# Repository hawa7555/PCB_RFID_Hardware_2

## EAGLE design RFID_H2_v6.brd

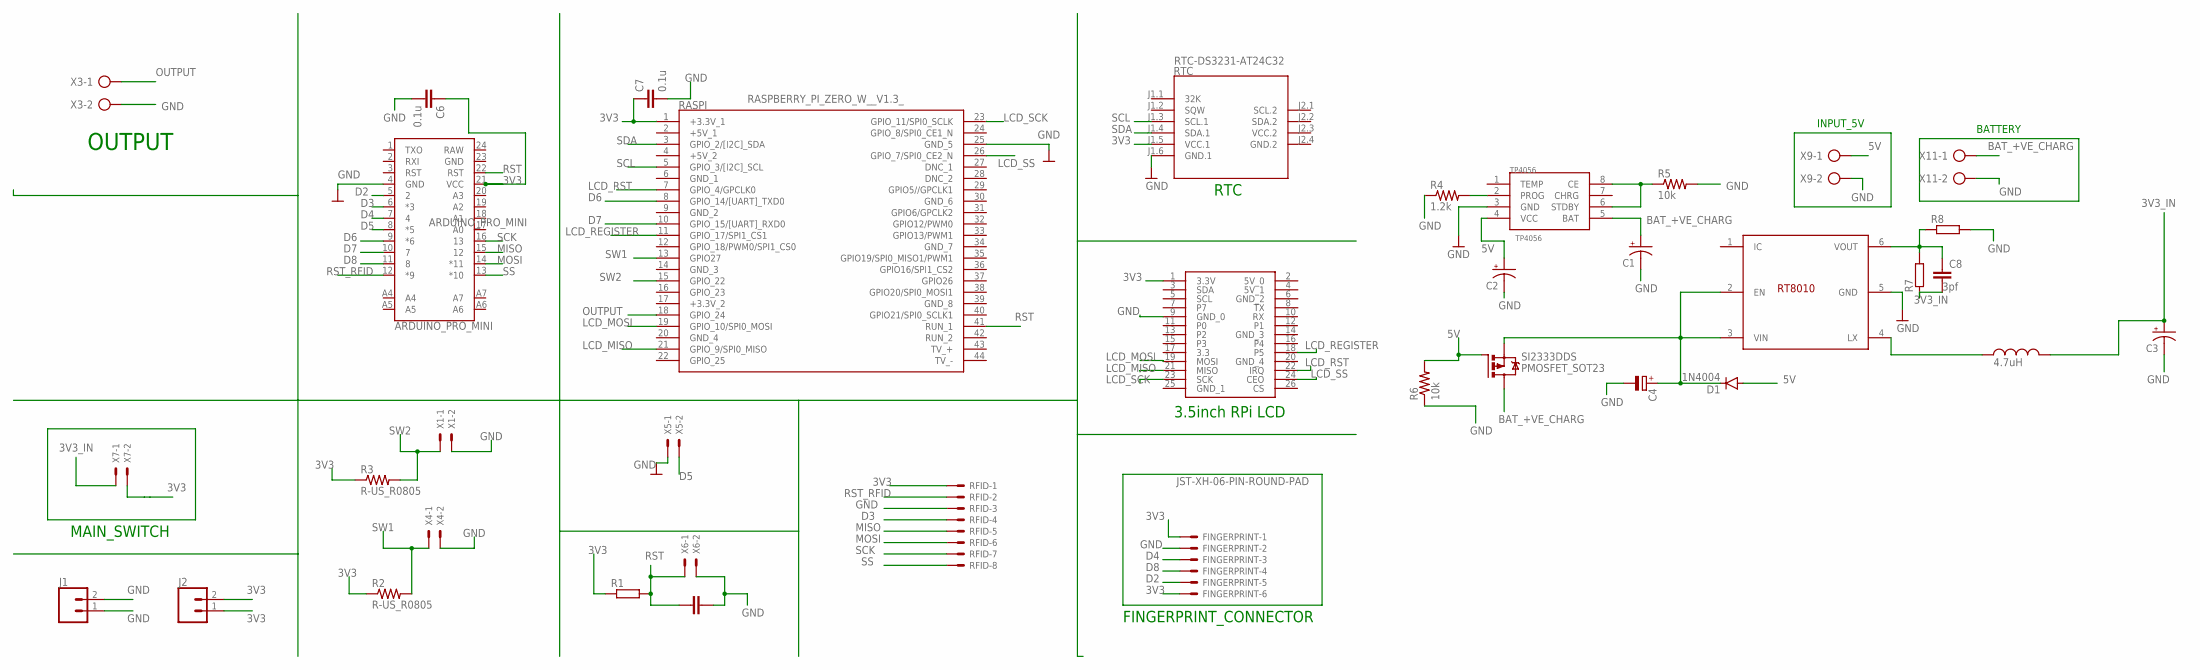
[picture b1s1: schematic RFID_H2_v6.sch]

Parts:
ARDUINO_PRO_MINI: ARDUINO_PRO_MINI
C1, C2, C3: 10uf; C/6032-28R
C4: 4.7uf; E2,5-6
C5: 10n; C0805K
C6, C7: 0.1u; C0805
C8: 3pf; C025-025X050
D1: 1N4004; DO41-10
FINGERPRINT: JST-XH-06-PIN-ROUND-PAD; JST-XH-06-PACKAGE-ROUND-PAD
J1, J2: CONN_02; 1X02
L2: 4.7uH; WE-TI_TIHV_8095
R1: R-EU_0204/5; 0204/5
R2, R3: R-US_R0805; R0805
R4: 1.2k; R0805
R5, R6: 10k; R0805
R7: 1.2M; 0204/7
R8: 270K; 0204/7
RASPI: RASPBERRY_PI_ZERO_W__V1.3_; RASPBERRYPIZEROWV13
RFID: JST-XH-08-PIN-ROUND-PAD; JST-XH-08-PACKAGE-ROUND-PAD
RT8010: RT8010_BUCK_CONVERTER; RT8010
RTC: RTC-DS3231-AT24C32
SI2333DDS: PMOSFET_SOT23; SOT23
TP4056: TP4056; SOP-8
U$7: 3.5_INCH_TOUCHSCREEN; FE13-2
X1, X4, X5, X6, X7: JST-XH-02-PIN-LONG-PAD; JST-XH-02-PACKAGE-LONG-PAD
X3, X9, X11: AK500/2-H

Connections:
3V3: ARDUINO_PRO_MINI.21 (VCC), C6.1, C7.1, FINGERPRINT.1, FINGERPRINT.6, J2.1, J2.2, R1.1, R2.1, R3.1, RASPI.1 (+3.3V_1), RFID.1, RTC.J1.5 (VCC.1), U$7.1 (3.3V), X7.2
3V3_IN: C3.+, C8.2, L2.2, R7.1, X7.1
5V: C2.+, D1.A, R6.2, SI2333DDS.1 (G), TP4056.4 (VCC), X9.1
BAT_+VE_CHARG: C1.+, SI2333DDS.3 (D), TP4056.5 (BAT), X11.1
D2: ARDUINO_PRO_MINI.5 (2), FINGERPRINT.5
D3: ARDUINO_PRO_MINI.6 (*3), RFID.4
D4: ARDUINO_PRO_MINI.7 (4), FINGERPRINT.3
D5: ARDUINO_PRO_MINI.8 (*5), X5.2
D6: ARDUINO_PRO_MINI.9 (*6), RASPI.8 (GPIO_14/[UART]_TXD0)
D7: ARDUINO_PRO_MINI.10 (7), RASPI.10 (GPIO_15/[UART]_RXD0)
D8: ARDUINO_PRO_MINI.11 (8), FINGERPRINT.4
GND: ARDUINO_PRO_MINI.4 (GND), ARDUINO_PRO_MINI.23 (GND), C1.-, C2.-, C3.-, C4.-, C5.1, C6.2, C7.2, FINGERPRINT.2, J1.1, J1.2, R4.1, R5.2, R6.1, R8.2, RASPI.25 (GND_5), RFID.3, RT8010.5 (GND), RTC.J1.6 (GND.1), TP4056.3 (GND), U$7.9 (GND_0), X1.2, X3.2, X4.2, X5.1, X6.2, X9.2, X11.2
GND.2: RTC.J2.4 (GND.2)
LCD_MISO: RASPI.21 (GPIO_9/SPI0_MISO), U$7.21 (MISO)
LCD_MOSI: RASPI.19 (GPIO_10/SPI0_MOSI), U$7.19 (MOSI)
LCD_REGISTER: RASPI.11 (GPIO_17/SPI1_CS1), U$7.18 (P5)
LCD_RST: RASPI.7 (GPIO_4/GPCLK0), U$7.22 (IRQ)
LCD_SCK: RASPI.23 (GPIO_11/SPI0_SCLK), U$7.23 (SCK)
LCD_SS: RASPI.26 (GPIO_7/SPI0_CE2_N), U$7.24 (CEO)
MISO: ARDUINO_PRO_MINI.15 (12), RFID.5
MOSI: ARDUINO_PRO_MINI.14 (*11), RFID.6
unnamed: C8.1, R7.2, R8.1, RT8010.6 (VOUT)
unnamed: R4.2, TP4056.2 (PROG)
unnamed: R5.1, TP4056.6 (STDBY), TP4056.8 (CE)
unnamed: L2.1, RT8010.4 (LX)
unnamed: C4.+, D1.C, RT8010.2 (EN), RT8010.3 (VIN), SI2333DDS.2 (S)
OUTPUT: RASPI.18 (GPIO_24), X3.1
RAW: ARDUINO_PRO_MINI.24 (RAW)
RST: ARDUINO_PRO_MINI.22 (RST), C5.2, R1.2, RASPI.41 (RUN_1), X6.1
RST_RFID: ARDUINO_PRO_MINI.12 (*9), RFID.2
SCK: ARDUINO_PRO_MINI.16 (13), RFID.7
SCL: RASPI.5 (GPIO_3/[I2C]_SCL), RTC.J1.3 (SCL.1)
SDA: RASPI.3 (GPIO_2/[I2C]_SDA), RTC.J1.4 (SDA.1)
SS: ARDUINO_PRO_MINI.13 (*10), RFID.8
SW1: R2.2, RASPI.13 (GPIO27), X4.1
SW2: R3.2, RASPI.15 (GPIO_22), X1.1
VCC.2: RTC.J2.3 (VCC.2)

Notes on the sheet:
FINGERPRINT_CONNECTOR
RTC
3.5inch RPi LCD
MAIN_SWITCH
INPUT_5V
BATTERY
OUTPUT

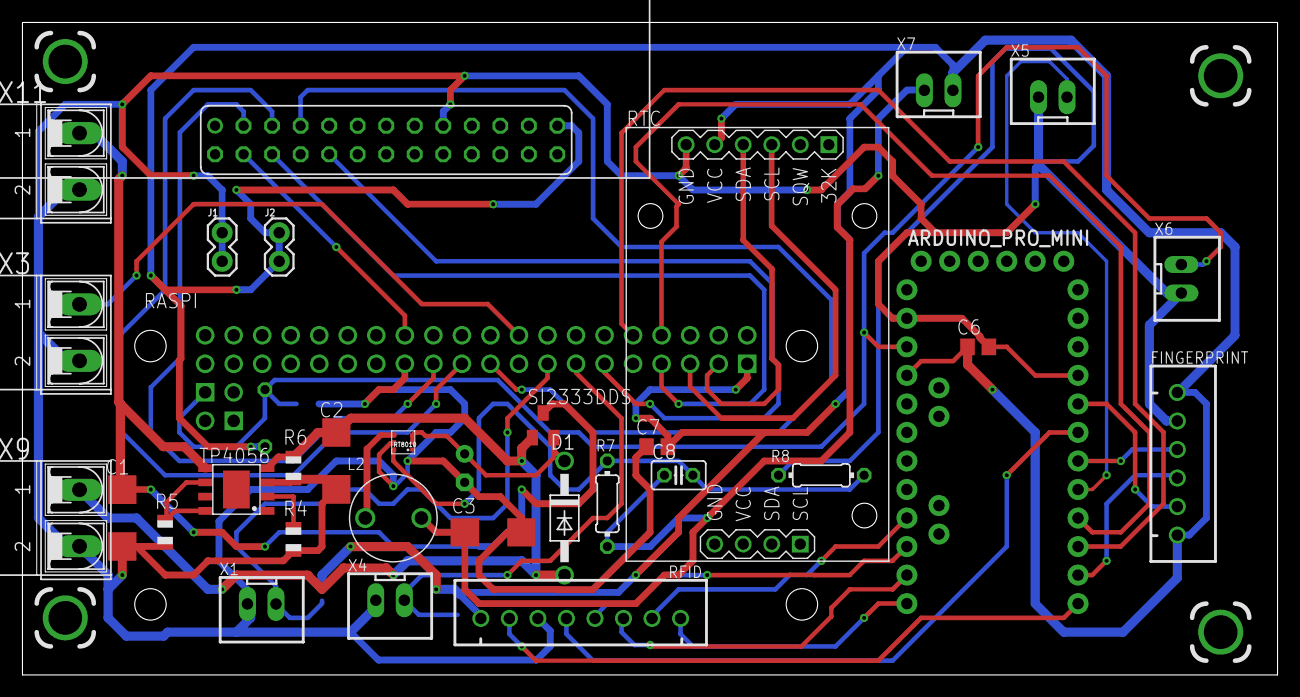
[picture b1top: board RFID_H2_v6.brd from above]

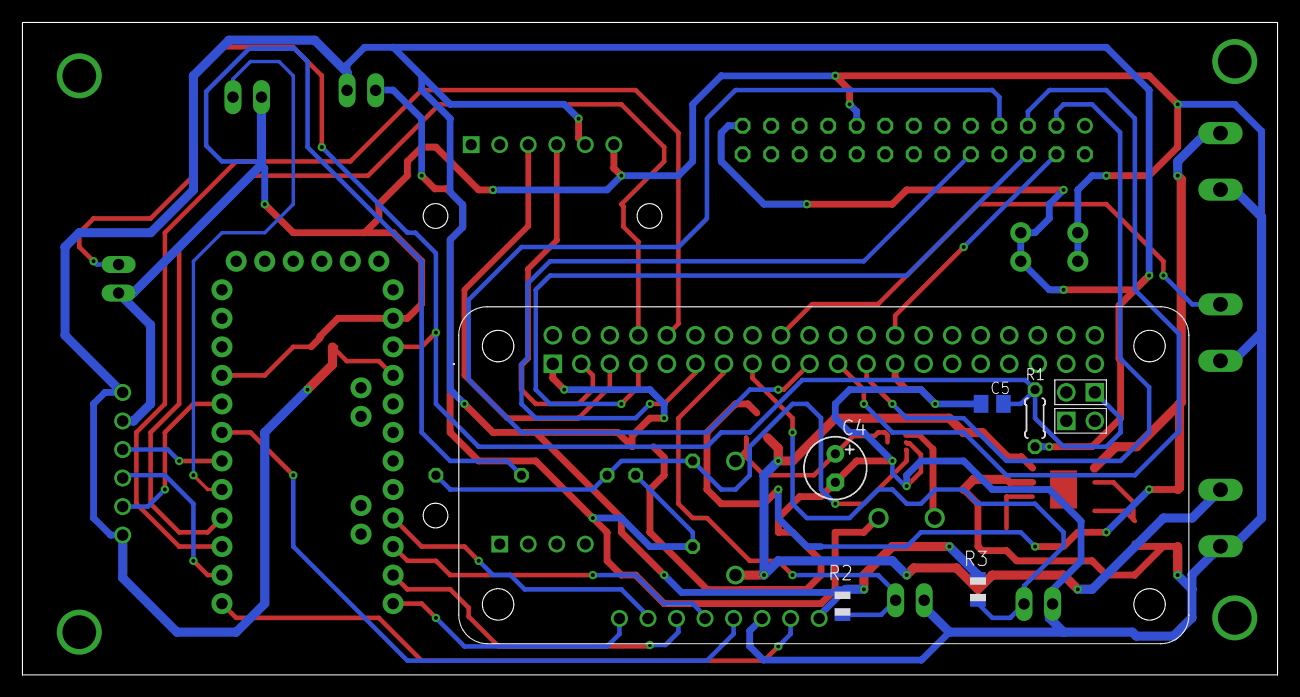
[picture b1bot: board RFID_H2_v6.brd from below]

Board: 2 copper layers, 111.7 x 58.1 mm, 37 parts (7 on the bottom side), 34 nets.

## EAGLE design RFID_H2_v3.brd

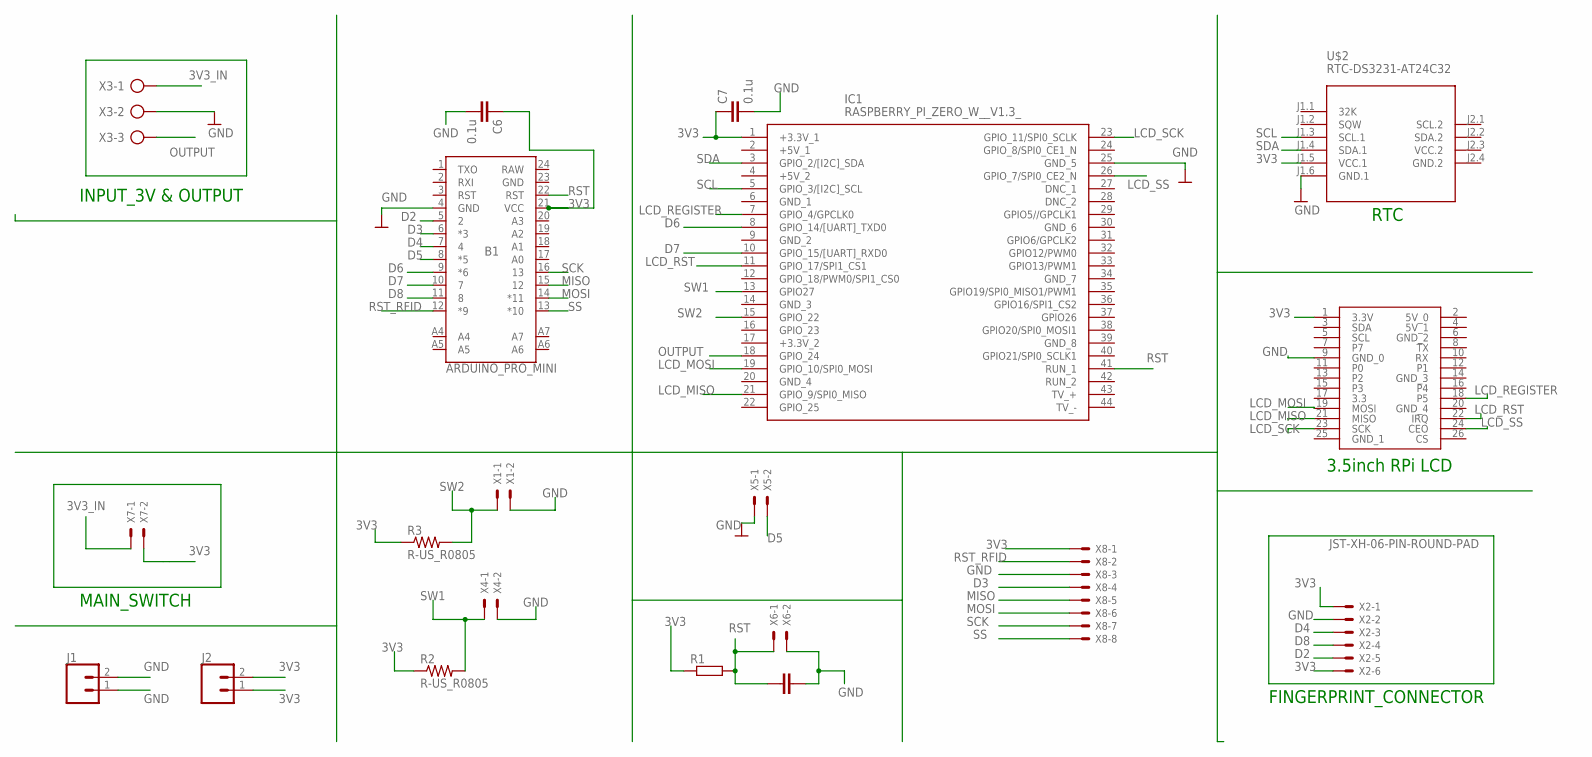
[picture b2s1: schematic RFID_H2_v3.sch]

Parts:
B1: ARDUINO_PRO_MINI
C5: 10n; C0805K
C6, C7: 0.1u; C0805
IC1: RASPBERRY_PI_ZERO_W__V1.3_; RASPBERRYPIZEROWV13
J1, J2: CONN_02; 1X02
R1: R-EU_0204/5; 0204/5
R2, R3: R-US_R0805; R0805
U$2: RTC-DS3231-AT24C32
U$7: 3.5_INCH_TOUCHSCREEN; FE13-2
X1, X4, X5, X6, X7: JST-XH-02-PIN-LONG-PAD; JST-XH-02-PACKAGE-LONG-PAD
X2: JST-XH-06-PIN-ROUND-PAD; JST-XH-06-PACKAGE-ROUND-PAD
X3: AK500/3-H
X8: JST-XH-08-PIN-ROUND-PAD; JST-XH-08-PACKAGE-ROUND-PAD

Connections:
3V3: B1.21 (VCC), C6.1, C7.1, IC1.1 (+3.3V_1), J2.1, J2.2, R1.1, R2.1, R3.1, U$2.J1.5 (VCC.1), U$7.1 (3.3V), X2.1, X2.6, X7.2, X8.1
3V3_IN: X3.1, X7.1
D2: B1.5 (2), X2.5
D3: B1.6 (*3), X8.4
D4: B1.7 (4), X2.3
D5: B1.8 (*5), X5.2
D6: B1.9 (*6), IC1.8 (GPIO_14/[UART]_TXD0)
D7: B1.10 (7), IC1.10 (GPIO_15/[UART]_RXD0)
D8: B1.11 (8), X2.4
GND: B1.4 (GND), B1.23 (GND), C5.1, C6.2, C7.2, IC1.25 (GND_5), J1.1, J1.2, U$2.J1.6 (GND.1), U$7.9 (GND_0), X1.2, X2.2, X3.2, X4.2, X5.1, X6.2, X8.3
GND.2: U$2.J2.4 (GND.2)
LCD_MISO: IC1.21 (GPIO_9/SPI0_MISO), U$7.21 (MISO)
LCD_MOSI: IC1.19 (GPIO_10/SPI0_MOSI), U$7.19 (MOSI)
LCD_REGISTER: IC1.7 (GPIO_4/GPCLK0), U$7.18 (P5)
LCD_RST: IC1.11 (GPIO_17/SPI1_CS1), U$7.22 (IRQ)
LCD_SCK: IC1.23 (GPIO_11/SPI0_SCLK), U$7.23 (SCK)
LCD_SS: IC1.26 (GPIO_7/SPI0_CE2_N), U$7.24 (CEO)
MISO: B1.15 (12), X8.5
MOSI: B1.14 (*11), X8.6
OUTPUT: IC1.18 (GPIO_24), X3.3
RAW: B1.24 (RAW)
RST: B1.22 (RST), C5.2, IC1.41 (RUN_1), R1.2, X6.1
RST_RFID: B1.12 (*9), X8.2
SCK: B1.16 (13), X8.7
SCL: IC1.5 (GPIO_3/[I2C]_SCL), U$2.J1.3 (SCL.1)
SDA: IC1.3 (GPIO_2/[I2C]_SDA), U$2.J1.4 (SDA.1)
SS: B1.13 (*10), X8.8
SW1: IC1.13 (GPIO27), R2.2, X4.1
SW2: IC1.15 (GPIO_22), R3.2, X1.1
VCC.2: U$2.J2.3 (VCC.2)

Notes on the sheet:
FINGERPRINT_CONNECTOR
RTC
3.5inch RPi LCD
MAIN_SWITCH
INPUT_3V & OUTPUT

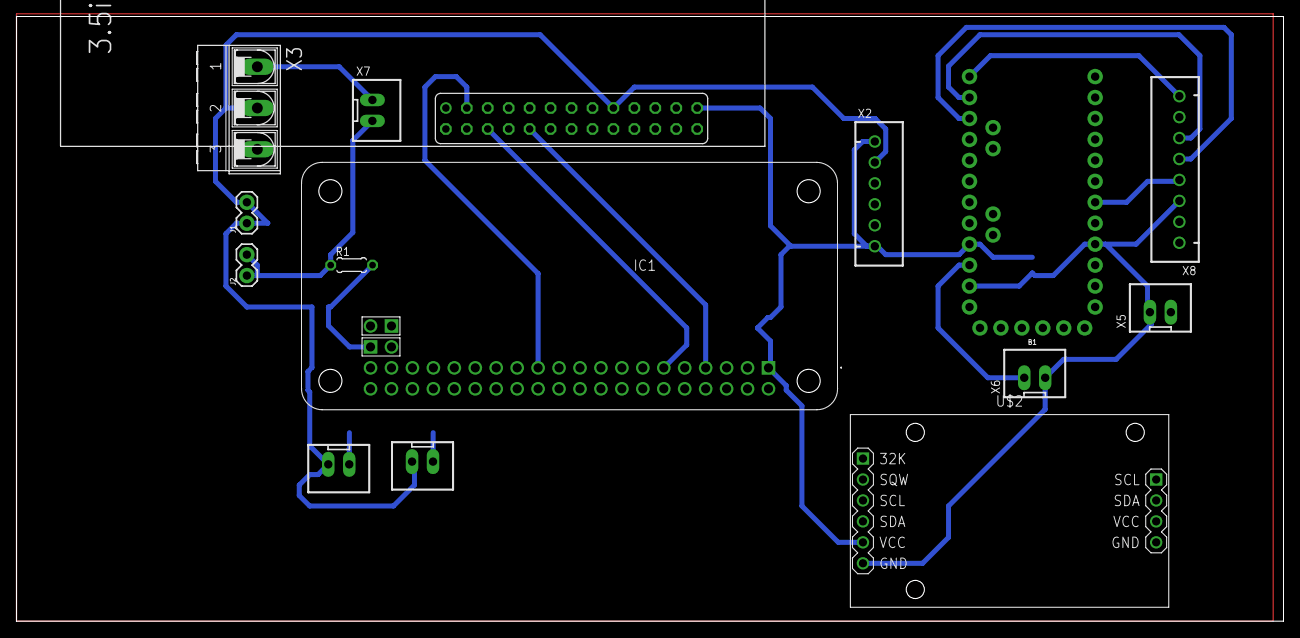
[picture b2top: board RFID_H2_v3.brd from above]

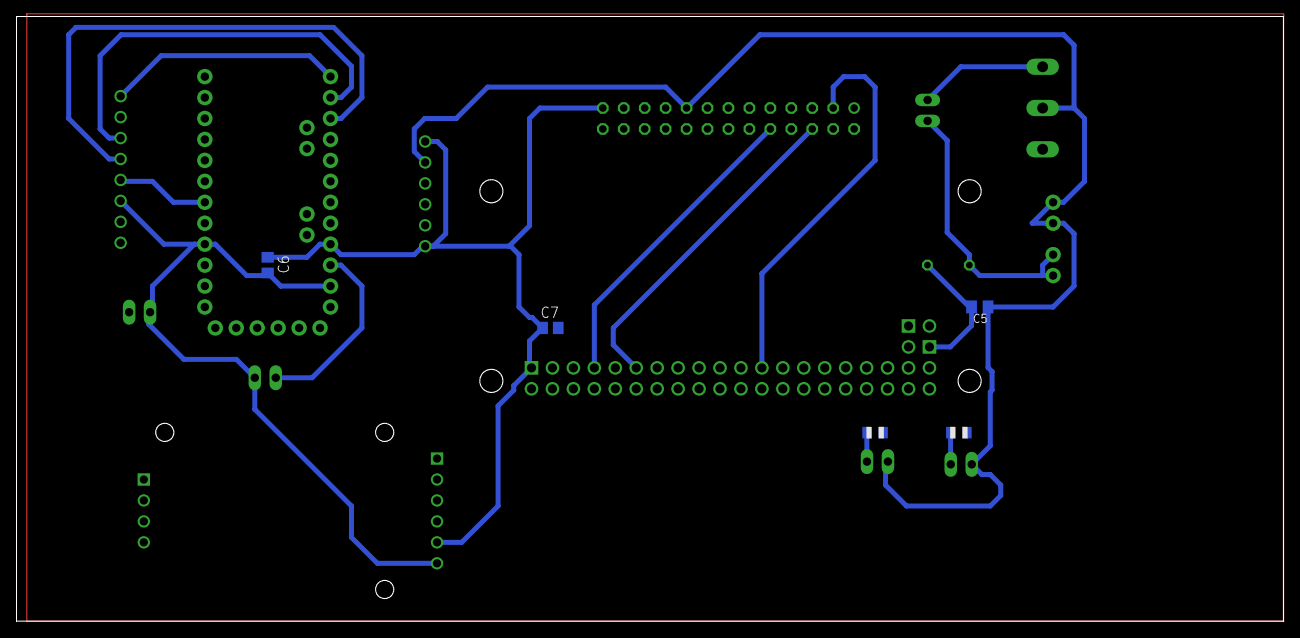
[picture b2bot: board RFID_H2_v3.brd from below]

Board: 2 copper layers, 153.7 x 73.3 mm, 20 parts (5 on the bottom side), 27 nets.

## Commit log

2020-05-14 Before 3.3v shifting and without level shifter
2020-05-16 Whole circuit on 3.3V logic level and no level shifter needed
2020-07-18 Final PCB

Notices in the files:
parts and their libraries:
SparkFun-Boards: Licensing: Creative Commons ShareAlike 4.0 International - https://creativecommons.org/licenses/by-sa/4.0
diy-modules: Released under the Creative Commons Attribution 4.0 International License: http://creativecommons.org/licenses/by/4.0
